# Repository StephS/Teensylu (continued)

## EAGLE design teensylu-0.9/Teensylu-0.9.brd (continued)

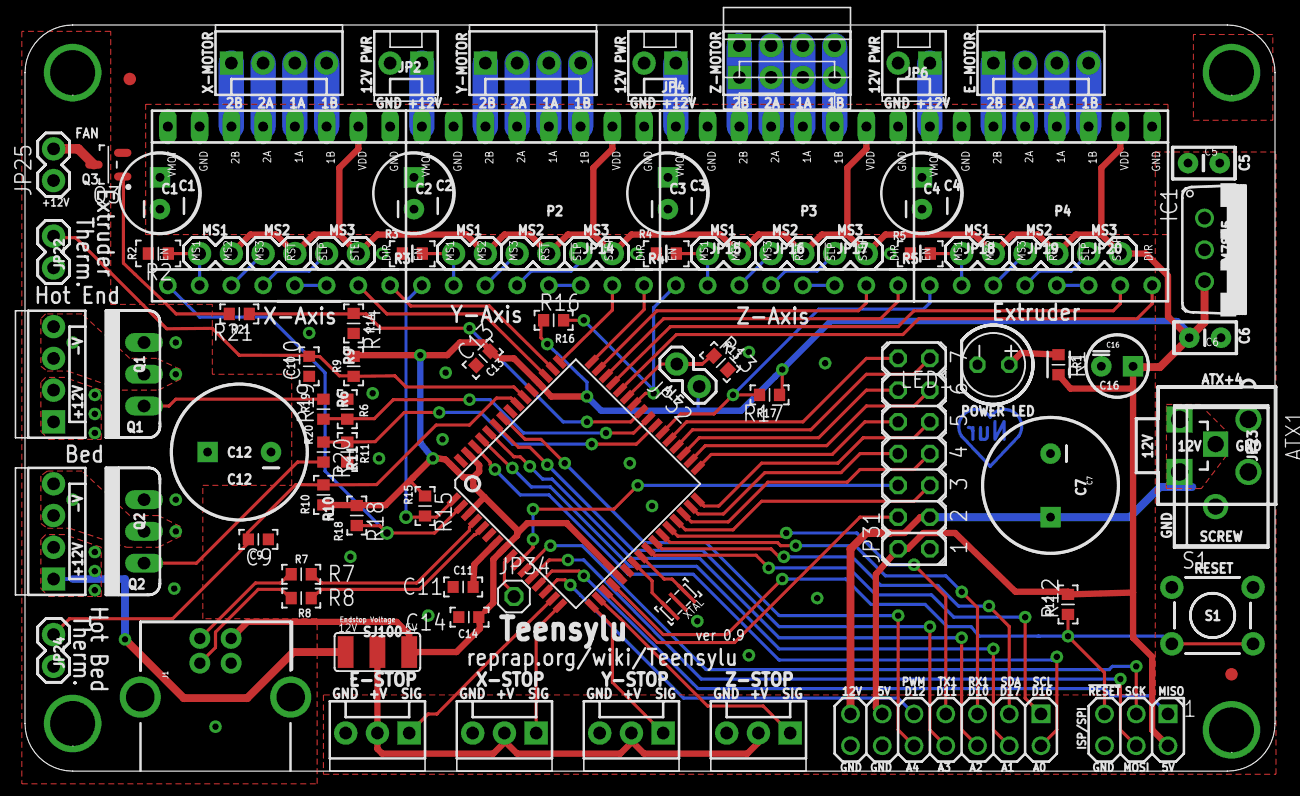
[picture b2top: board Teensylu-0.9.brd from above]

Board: 2 copper layers, 100.0 x 59.7 mm, 89 parts (0 on the bottom side), 98 nets.

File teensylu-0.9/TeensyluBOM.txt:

Teensylu Bill of Materials 'working' version
===============================

ATX1                     ATX-4VERTICAL                    MINIFITJR-4-VERTICAL   
C1 - C4                  100uf                            CPOL-RADIAL-100UF-35V  
C5                       0.33uF                           CAP-PTH-SMALL2         
C6                       0.1uF                            CAP-PTH-SMALL2         
C9,C10                   10uF                             CAPC2012X145AN         
C11                      1uf                              CAPC2012X145AN         
C7,C12                   580uF                           CPOL-RADIAL-580UF-35V 
C13,C14                  0.1uF                            CAPC2012X145AN         
C16                      4.7uF                            CPOL-RADIAL-10UF-35V   
HDDPWR                   5v/12v                           HDD-VERTICAL           
IC1                      LM7805                           VREG-NOGND             
IC2                      AT90USB1286                      TQFP64                 
J1                       USB                              USB-B-PTH              
JP1,JP3,JP5,JP7          MOT-X, MOT-Y, MOT-Z, MOT-E       MOLEX-1X4              
JP2,JP4,JP6,JP8          12VPWR                           MOLEX-1X2              
JP9 - JP20               Motor Selects                    1X02               
JP8,JP21                 HOTEND,HOTBED                    MOLEX-1X4
JP22, JP24,JP25          Thermistors,FAN                  1X02                   
JP27,JP28,JP29,JP30      X-STOP,Y-STOP,Z-STOP,E-STOP      MOLEX-1X3              
JP31                     2x7                              JP7Q                   
JP32                     ALE                              1X02                   
LED1                                                      LED5MM                 
P1 - P4                  POLOLU                           POLOLU-ALLEGRO-PTH     
Q1,Q2                    STP45NF06                        TO220V                 
Q3                       PMV45EN                          SOT95P280X135-3N       
R1                       1k                             RESC2012X70N           
R2 - R5, R12             100k                             RESC2012X70N           
R6, R11, R14             10k                              RESC2012X70N           
R7, R8 	                 22 Ohm                           RESC2012X70N           
R9, R10                  4.7k                             RESC2012X70N           
R13                      1k                               RESC2012X70N           
S1                       RESET                            TACTILE-PTH            
SJ100                    5v/12v                           SJ_3                   
XTAL                     16MHZ RESONATOR                  PRQC_3.2X1.3_RESONATOR 
R19, R20, R21            100

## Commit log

2011-04-28 Checking in lost files.
2011-04-30 Lots of changes. Added Enable Pin to each motor controller, Extra I/O header is now reduced to 7x2 header. Cleaned up routing. Moved 4.7uF cap to 5v Input (Value may change). Added pullup jumper to A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
2011-05-01 Added Version number to silkscreen.
2011-05-01 create 0.5 revision folder with images and gerbers
2011-05-01 updated working
2011-05-01 Swapped pins to add PWM to expansion header.
2011-05-02 Updating working folder.
2011-05-08 Adding a BOM for the current working version and v0.6
2011-05-08 Changing caps to 35v
2011-05-08 Cleaned up the BOM some more. TODO: Seperate optional components.
2011-06-25 Added C7, changed C12 capacitance to 580uF to reduce physical dimensions. Changed Expansion header to match sanguinololu rev 1.2 expansion header. Changed package of MCU to meet specs for better sold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
2011-06-25 Updated working to rev 0.7
2011-06-30 R13 changed to 10k. Smaller BOM, save in bulk.
2011-11-03 Added 4 new 100k resistors to pullup stepper motor enable pins during programming. Also added second header for Z motor output (Prusa Mendel Friendly!). Still needs some minor tweaking to silkscreen 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
2013-10-01 Added 100 ohm resistors to Mosfets. Changed ALL SMD components to 0603.
    I added a 100 ohm resistor to the gate of every mosfet. this should help
    prevent damage to the MCU.
    I changed all of the SMD components to 0603. I've been wanting to do
    this for a while. They're not much smaller than 0805, but it allows me
    to route things better.
2014-06-02 Added warning
    Recommending the Teensylu not to be used until changes and modifications
    are made. This is based on the risk of damage or fire! Either do not use
    the board or take proper precautions!
    There is no such thing as a "Safe" 3d printer controller. Keep a smoke
    detector nearby and have a fire extinguisher handy. Do NOT leave
    unattended.
2015-05-18 New TeensyluV1
    The TeensyluV1 is a redesign of the Teensylu board. I have backported
    many of the features of the Teensylu2 board, and added new features like
    a blade fuse. I highly recommend using the V1 over the original Teensylu
    board.
2015-07-10 Fixed Z endstop
    Collector and emitter pins were swapped.
2015-08-25 Now with 4 layers!
    The board is now 4 layers. This is to allow high current through the
    planes. It also means less via's.
2015-09-03 Adding 2 Layer board
    I decided that a 2 Layer board would be a cost effective option. I
    pulled the last 2 Layer board and cleaned it up.
2015-09-14 Updated USB Diode, Added Jumper Wires, Z Endstop is now 4 pin
    The USB Diode has been changed to DRTR5V0U2SR
    22ga jumper wires added to increase current capacity
    Z Endstop header is now 4 pin. All future versions will use 4 pin
    endstop on Z. See schematics and set the appropriate pinout for your
    configuration.
2015-09-16 Updated heater mosfets
    I updated the heater mosfets to 40v version, part # PSMN1R8-40YLC,115
2015-09-16 minor routing changes
    just a few changes to clean up routing.
2015-11-09 Added dimensions
    Dimensions are added to make it easier to make enclosures.
